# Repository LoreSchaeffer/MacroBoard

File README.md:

# MacroBoard

A macro keyboard with programmable keys, RGB leds, programmable slider potentiometers and a lot of expandability through I2C and UART.

### Features
- [x] 13 programmable cherry switch keys
- [x] 13 RGB addressable leds
- [x] 5 slider potentiometers
- [x] WiFi and Bluetooth connectivity
- [x] Battery input (5V)
- [x] 5V and 3.3V power outputs
- [x] I2C expansion port
- [x] UART expansion port
- [x] LED data expansion port
- [ ] 3D printable case
- [ ] Firmware
- [ ] Software

## Contributing
To contribute to this repository just fork this repository make your changes or add your code and make a pull request.

## License
MacroBoard is released under the MIT license. You can find a copy [here](https://github.com/LoreSchaeffer/MacroBoard/blob/master/LICENSE)

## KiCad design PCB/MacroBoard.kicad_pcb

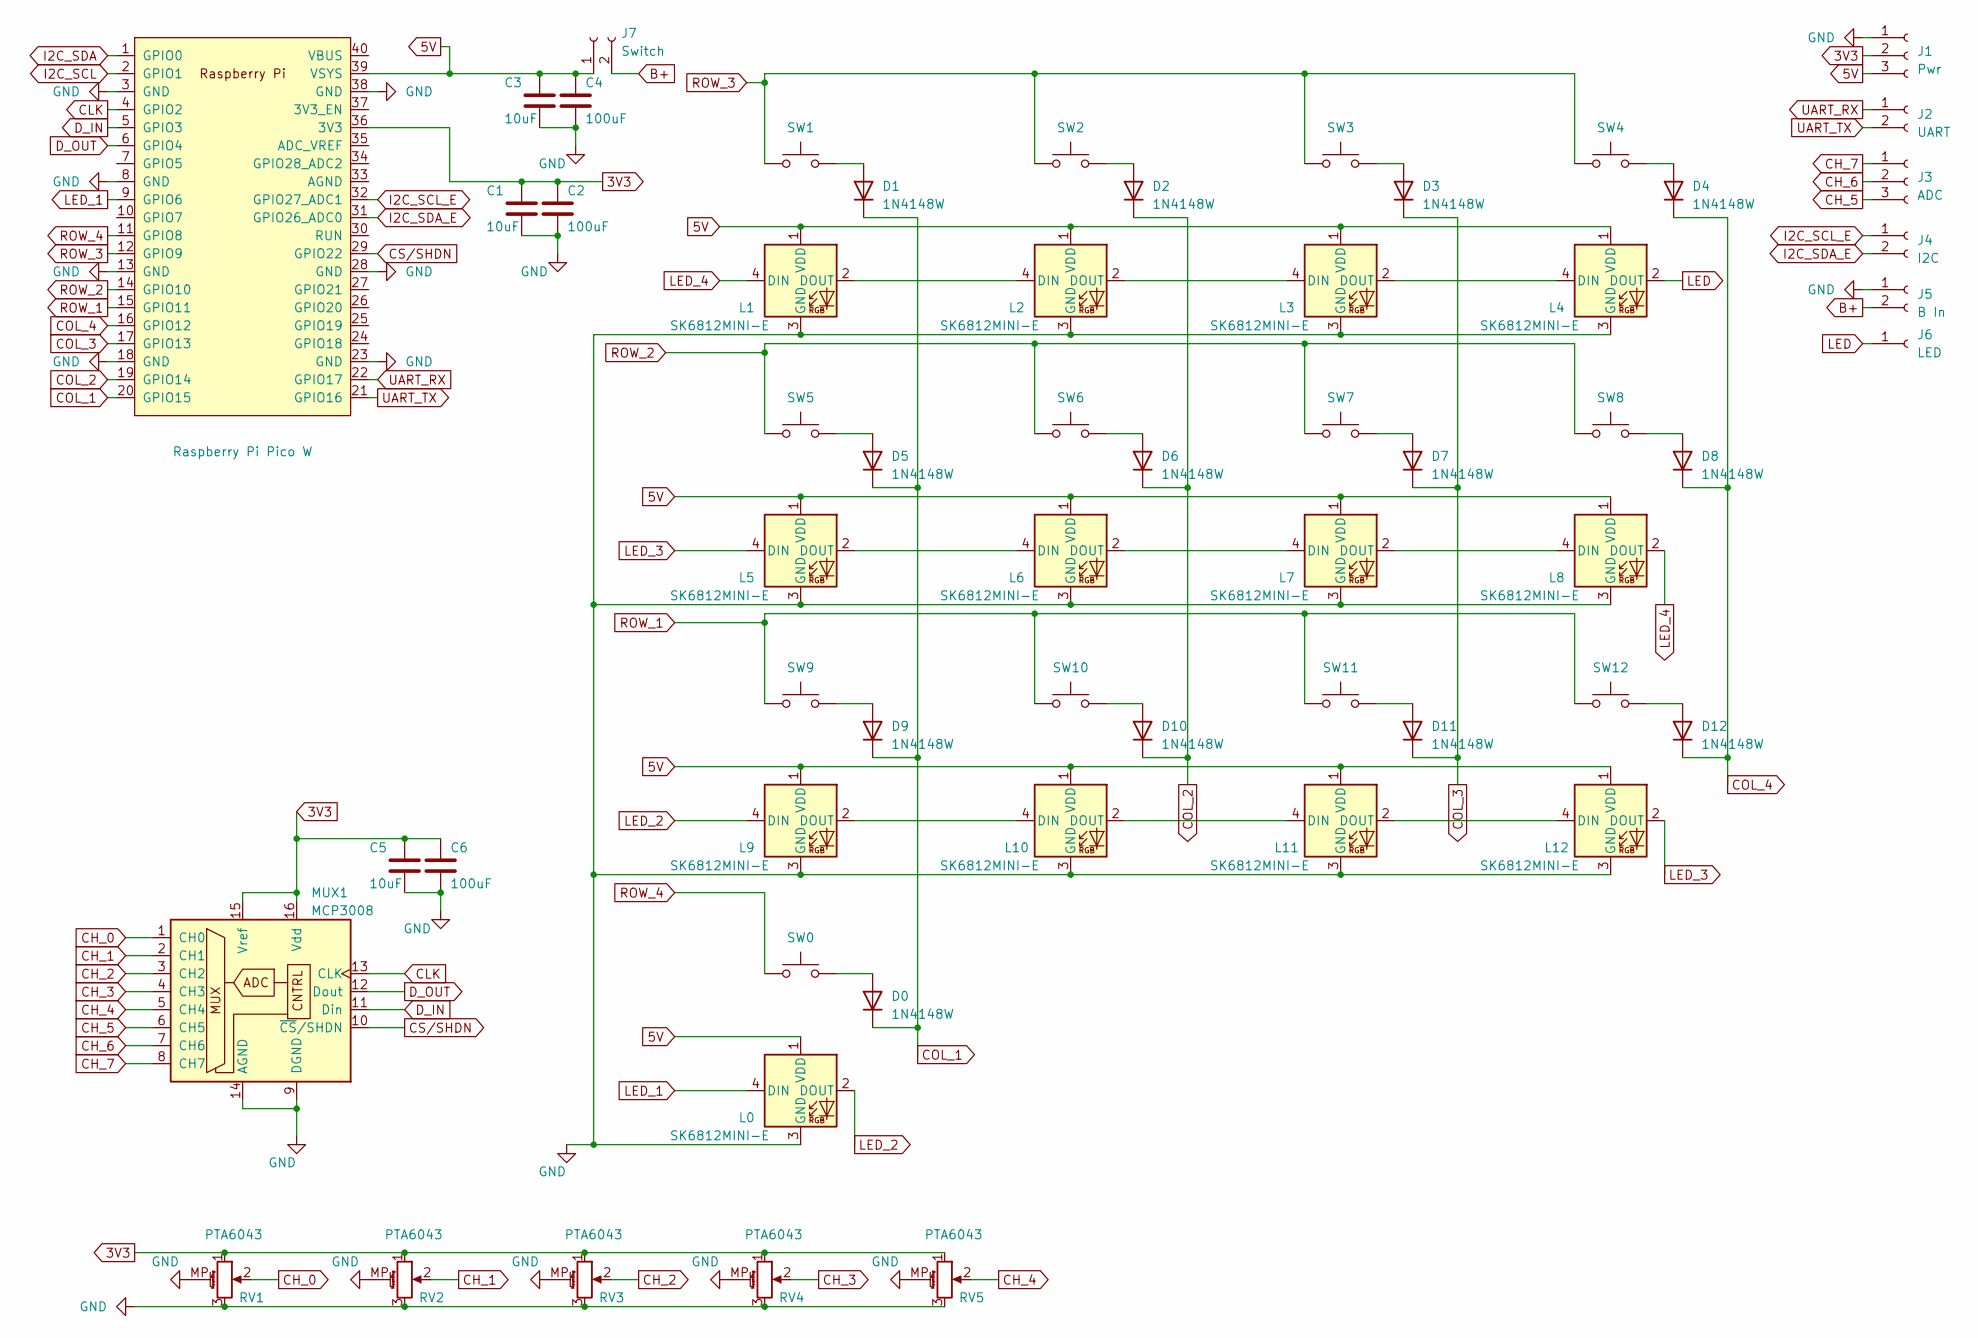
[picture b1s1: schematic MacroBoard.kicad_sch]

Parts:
C1, C3, C5: 10uF; C_1206_3216Metric
C2, C4, C6: 100uF; C_1206_3216Metric
D0, D1, D2, D3, D4, D5, D6, D7, D8, D9, D10, D11, D12: 1N4148W; D_SOD-123
J1: Pwr; PinHeader_1x03_P2.54mm_Vertical
J2: UART; PinHeader_1x02_P2.54mm_Vertical
J3: ADC; PinHeader_1x03_P2.54mm_Vertical
J4: I2C; PinHeader_1x02_P2.54mm_Vertical
J5: B In; PinHeader_1x02_P2.54mm_Vertical
J6: LED; Pin_D0.7mm_L6.5mm_W1.8mm_FlatFork
J7: Switch; PinHeader_1x02_P2.54mm_Vertical
L0, L1, L2, L3, L4, L5, L6, L7, L8, L9, L10, L11, L12: SK6812MINI-E; SK6812MINIE
MUX1: MCP3008; DIP-16_W7.62mm
RPPW1: Raspberry Pi Pico W; MODULE_SC0918
RV1, RV2, RV3, RV4, RV5: PTA6043; Potentiometer_Bourns_PTA6043_Single_Slide
SW0, SW1, SW2, SW3, SW4, SW5, SW6, SW7, SW8, SW9, SW10, SW11, SW12: SW_Push; SW_Cherry_MX_1.00u_Plate

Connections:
3V3: C1.1, C2.1, C5.1, C6.1, J1.2, MUX1.15 (Vref), MUX1.16 (Vdd), RPPW1.36 (3V3), RV1.1, RV2.1, RV3.1, RV4.1, RV5.1
5V: C3.1, C4.1, J1.3, J7.1, L0.1 (VDD), L1.1 (VDD), L2.1 (VDD), L3.1 (VDD), L4.1 (VDD), L5.1 (VDD), L6.1 (VDD), L7.1 (VDD), L8.1 (VDD), L9.1 (VDD), L10.1 (VDD), L11.1 (VDD), L12.1 (VDD), RPPW1.39 (VSYS)
B+: J5.2, J7.2
CH_0: MUX1.1 (CH0), RV1.2
CH_1: MUX1.2 (CH1), RV2.2
CH_2: MUX1.3 (CH2), RV3.2
CH_3: MUX1.4 (CH3), RV4.2
CH_4: MUX1.5 (CH4), RV5.2
CH_5: J3.3, MUX1.6 (CH5)
CH_6: J3.2, MUX1.7 (CH6)
CH_7: J3.1, MUX1.8 (CH7)
CLK: MUX1.13 (CLK), RPPW1.4 (GPIO2)
COL_1: D0.1 (K), D1.1 (K), D5.1 (K), D9.1 (K), RPPW1.20 (GPIO15)
COL_2: D2.1 (K), D6.1 (K), D10.1 (K), RPPW1.19 (GPIO14)
COL_3: D3.1 (K), D7.1 (K), D11.1 (K), RPPW1.17 (GPIO13)
COL_4: D4.1 (K), D8.1 (K), D12.1 (K), RPPW1.16 (GPIO12)
CS/SHDN: MUX1.10 (~CS/SHDN), RPPW1.29 (GPIO22)
D_IN: MUX1.11 (Din), RPPW1.5 (GPIO3)
D_OUT: MUX1.12 (Dout), RPPW1.6 (GPIO4)
GND: C1.2, C2.2, C3.2, C4.2, C5.2, C6.2, J1.1, J5.1, L0.3 (GND), L1.3 (GND), L2.3 (GND), L3.3 (GND), L4.3 (GND), L5.3 (GND), L6.3 (GND), L7.3 (GND), L8.3 (GND), L9.3 (GND), L10.3 (GND), L11.3 (GND), L12.3 (GND), MUX1.9 (DGND), MUX1.14 (AGND), RPPW1.3 (GND), RPPW1.8 (GND), RPPW1.13 (GND), RPPW1.18 (GND), RPPW1.23 (GND), RPPW1.28 (GND), RPPW1.38 (GND), RV1.3, RV1.MP (MountPin), RV2.3, RV2.MP (MountPin), RV3.3, RV3.MP (MountPin), RV4.3, RV4.MP (MountPin), RV5.3, RV5.MP (MountPin)
I2C_SCL: RPPW1.2 (GPIO1)
I2C_SCL_E: J4.1, RPPW1.32 (GPIO27_ADC1)
I2C_SDA: RPPW1.1 (GPIO0)
I2C_SDA_E: J4.2, RPPW1.31 (GPIO26_ADC0)
LED: J6.1, L4.2 (DOUT)
LED_1: L0.4 (DIN), RPPW1.9 (GPIO6)
LED_2: L0.2 (DOUT), L9.4 (DIN)
LED_3: L5.4 (DIN), L12.2 (DOUT)
LED_4: L1.4 (DIN), L8.2 (DOUT)
unnamed: D0.2 (A), SW0.2
unnamed: D1.2 (A), SW1.2
unnamed: D2.2 (A), SW2.2
unnamed: D3.2 (A), SW3.2
unnamed: D4.2 (A), SW4.2
unnamed: D5.2 (A), SW5.2
unnamed: D6.2 (A), SW6.2
unnamed: D7.2 (A), SW7.2
unnamed: D8.2 (A), SW8.2
unnamed: D9.2 (A), SW9.2
unnamed: D10.2 (A), SW10.2
unnamed: D11.2 (A), SW11.2
unnamed: D12.2 (A), SW12.2
unnamed: L1.2 (DOUT), L2.4 (DIN)
unnamed: L2.2 (DOUT), L3.4 (DIN)
unnamed: L3.2 (DOUT), L4.4 (DIN)
unnamed: L5.2 (DOUT), L6.4 (DIN)
unnamed: L6.2 (DOUT), L7.4 (DIN)
unnamed: L7.2 (DOUT), L8.4 (DIN)
unnamed: L9.2 (DOUT), L10.4 (DIN)
unnamed: L10.2 (DOUT), L11.4 (DIN)
unnamed: L11.2 (DOUT), L12.4 (DIN)
ROW_1: RPPW1.15 (GPIO11), SW9.1, SW10.1, SW11.1, SW12.1
ROW_2: RPPW1.14 (GPIO10), SW5.1, SW6.1, SW7.1, SW8.1
ROW_3: RPPW1.12 (GPIO9), SW1.1, SW2.1, SW3.1, SW4.1
ROW_4: RPPW1.11 (GPIO8), SW0.1
UART_RX: J2.1, RPPW1.22 (GPIO17)
UART_TX: J2.2, RPPW1.21 (GPIO16)

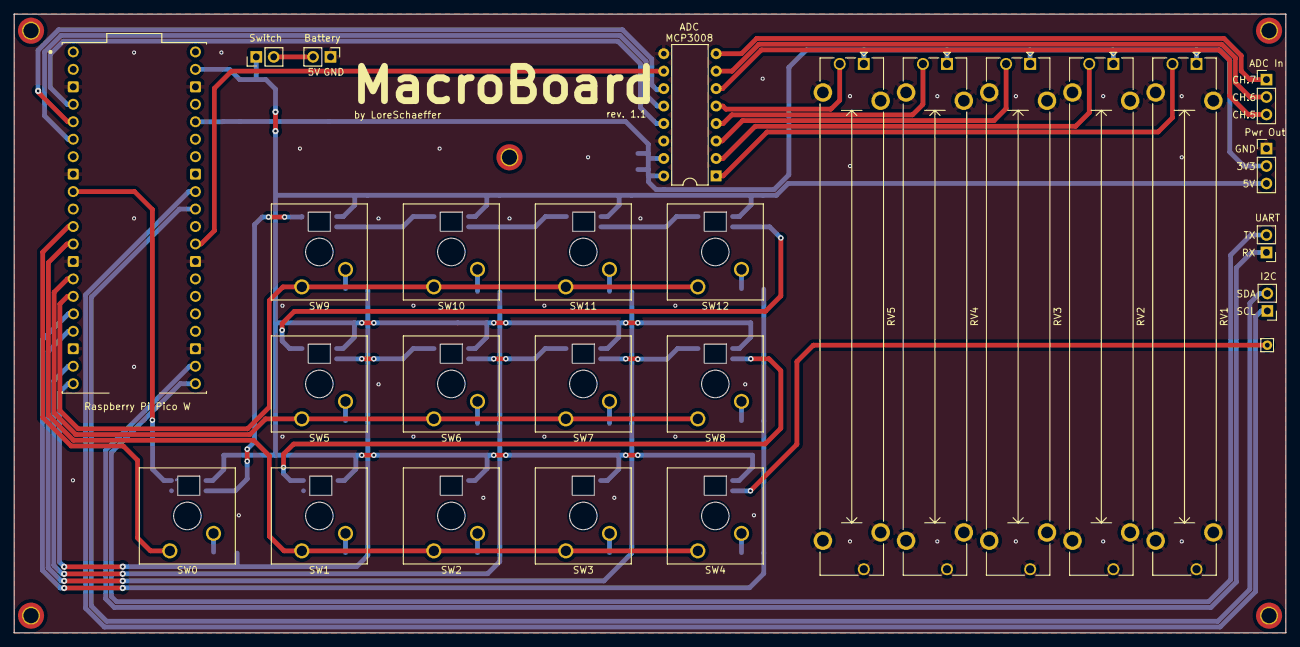
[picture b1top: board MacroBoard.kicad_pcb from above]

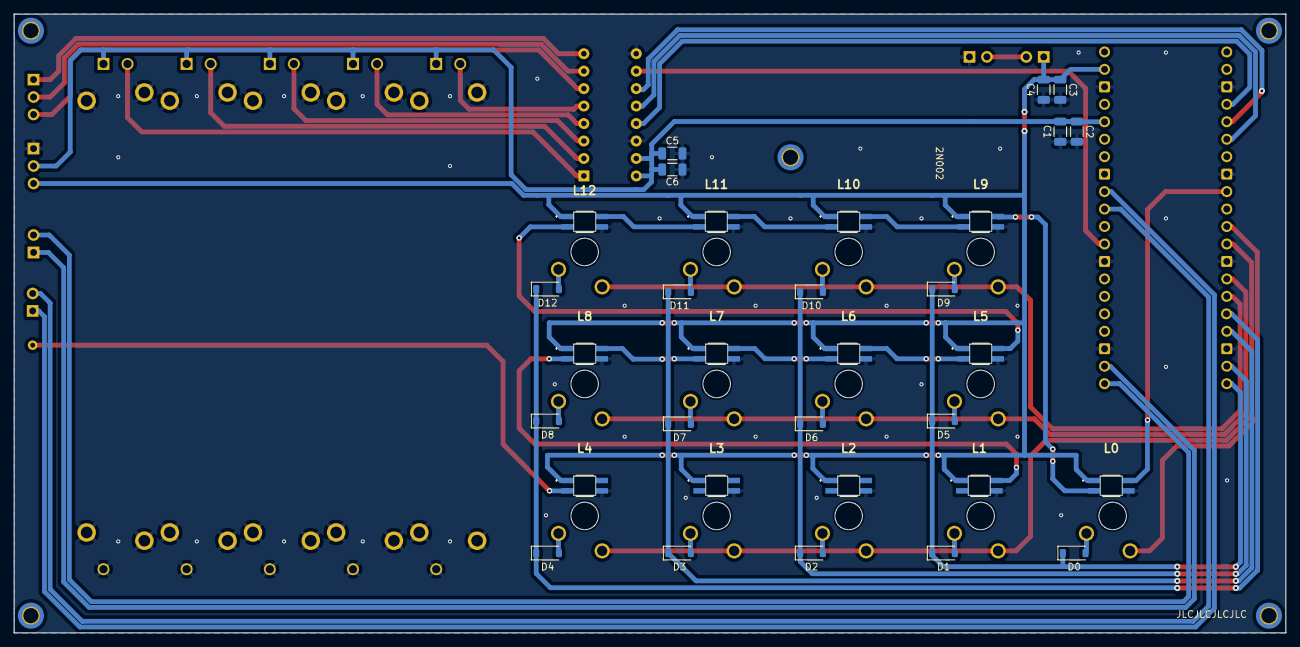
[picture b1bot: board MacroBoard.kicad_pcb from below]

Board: 2 copper layers, 185.0 x 90.0 mm, 59 parts (32 on the bottom side), 55 nets.

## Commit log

2023-06-15 Increased power tracks width
2023-06-15 New LED Footprint, new routings
2023-06-15 Fixed some routing issues, changed some tracks to reduce interference, added silkscreen
2023-06-18 Updated PCB, increased tracks and vias size, added level converter
2023-06-18 Added image to README
2023-06-18 Added silkscreen
2023-10-03 Adding code
2023-10-14 Revision 1.1 (Firmware WIP)
2024-01-10 Before TinyEKF
2024-01-11 ADC working (to refine)
